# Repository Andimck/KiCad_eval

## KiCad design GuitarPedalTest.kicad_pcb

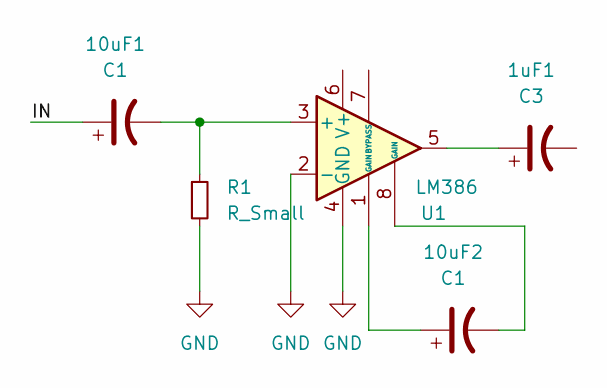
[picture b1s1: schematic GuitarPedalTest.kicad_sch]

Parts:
1uF1: C3
10uF1, 10uF2: C1
R1: R_Small
U1: LM386

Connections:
/IN: 10uF1.1
GND: R1.2, U1.2 (-), U1.4 (GND)
unnamed: 1uF1.1, U1.5
unnamed: 10uF1.2, R1.1, U1.3 (+)
unnamed: 10uF2.1, U1.1 (GAIN)
unnamed: 10uF2.2, U1.8 (GAIN)

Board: 2 copper layers, 5 parts (0 on the bottom side), 5 nets, no tracks yet.

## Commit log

2022-12-12 Added test file
2022-12-15 Testcommitblank
2022-12-15 Kicad test
